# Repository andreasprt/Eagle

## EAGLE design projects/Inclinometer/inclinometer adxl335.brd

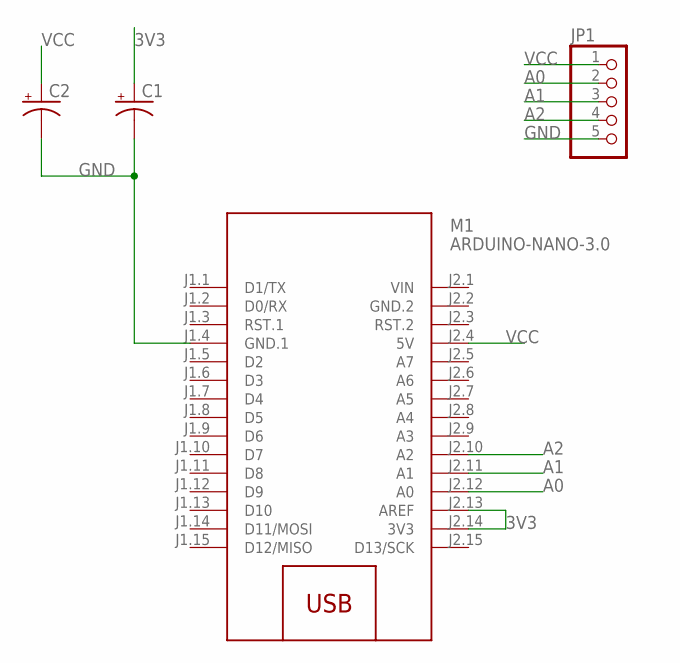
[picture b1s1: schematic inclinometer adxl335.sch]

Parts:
C1, C2: CPOL-USE2.5-6; E2,5-6
JP1: PINHD-1X5; 1X05
M1: ARDUINO-NANO-3.0

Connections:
3V3: C1.+, M1.J2.13 (AREF), M1.J2.14 (3V3)
A0: JP1.2, M1.J2.12 (A0)
A1: JP1.3, M1.J2.11 (A1)
A2: JP1.4, M1.J2.10 (A2)
GND: C1.-, C2.-, JP1.5, M1.J1.4 (GND.1)
GND.2: M1.J2.2 (GND.2)
VCC: C2.+, JP1.1, M1.J2.4 (5V)
VIN: M1.J2.1 (VIN)

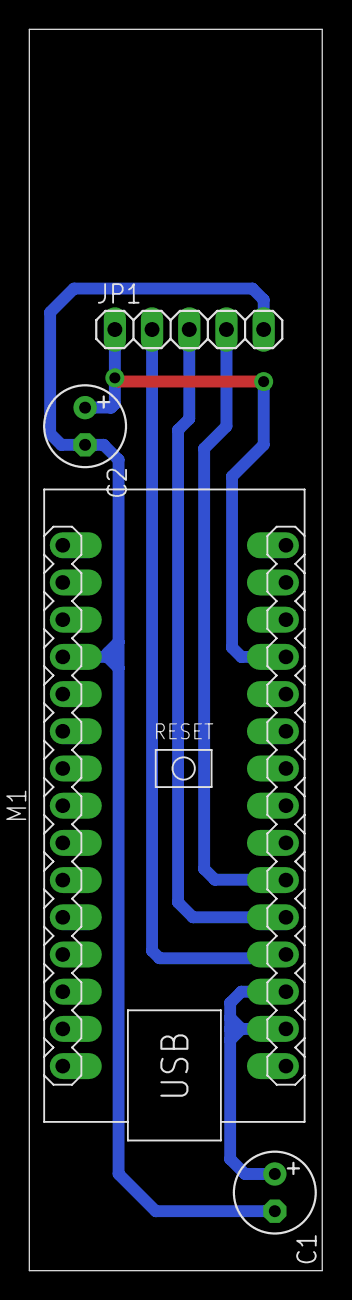
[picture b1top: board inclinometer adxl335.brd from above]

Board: 2 copper layers, 20.0 x 84.8 mm, 4 parts (0 on the bottom side), 6 nets.

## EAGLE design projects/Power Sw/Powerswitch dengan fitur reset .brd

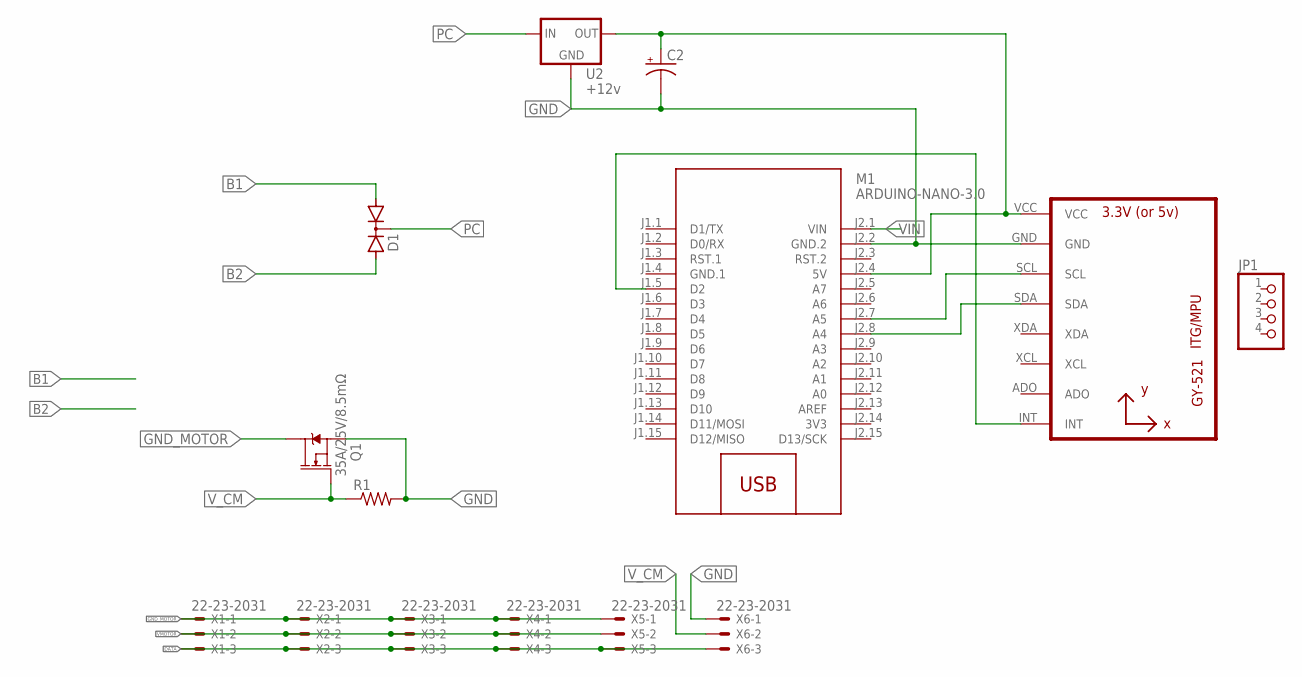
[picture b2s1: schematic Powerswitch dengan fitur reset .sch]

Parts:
C2: CPOL-USE2-5; E2-5
D1: DIODE-2AC|CATO220H; TO220AB
JP1: PINHD-1X4; 1X04
M1: ARDUINO-NANO-3.0
Q1: 35A/25V/8.5mΩ; DPAK
R1: R-US_0207/10; 0207/10
U1: GY-521MPU6050; GY-521
U2: +12v; TO-252
X1, X2, X3, X4, X5, X6: 22-23-2031

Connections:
3V3: M1.J2.14 (3V3)
B1: D1.A1
B2: D1.A2
DATA: X1.3, X2.3, X3.3, X4.3, X5.3, X6.3
GND: C2.-, M1.J2.2 (GND.2), Q1.3 (S), R1.2, U1.GND, U2.3 (GND), X6.1
GND.1: M1.J1.4 (GND.1)
GND_MOTOR: Q1.4 (D), X1.1, X2.1, X3.1, X4.1, X5.1
unnamed: M1.J2.8 (A4), U1.SDA
unnamed: M1.J2.7 (A5), U1.SCL
unnamed: M1.J1.5 (D2), U1.INT
unnamed: C2.+, M1.J2.4 (5V), U1.VCC, U2.2 (OUT)
PC: D1.C, U2.1 (IN)
VIN: M1.J2.1 (VIN)
VMOTOR: X1.2, X2.2, X3.2, X4.2, X5.2
V_CM: Q1.1 (G), R1.1, X6.2

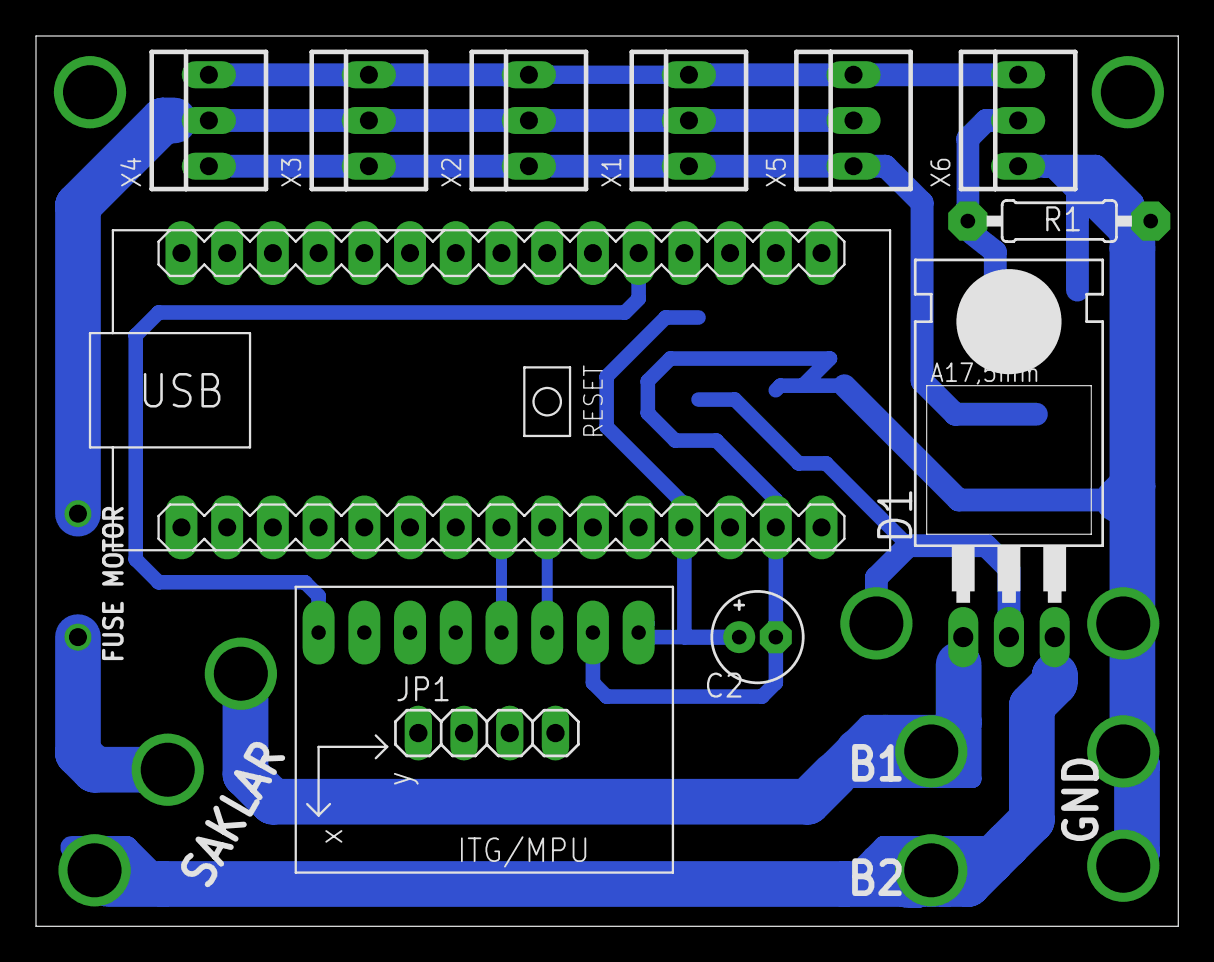
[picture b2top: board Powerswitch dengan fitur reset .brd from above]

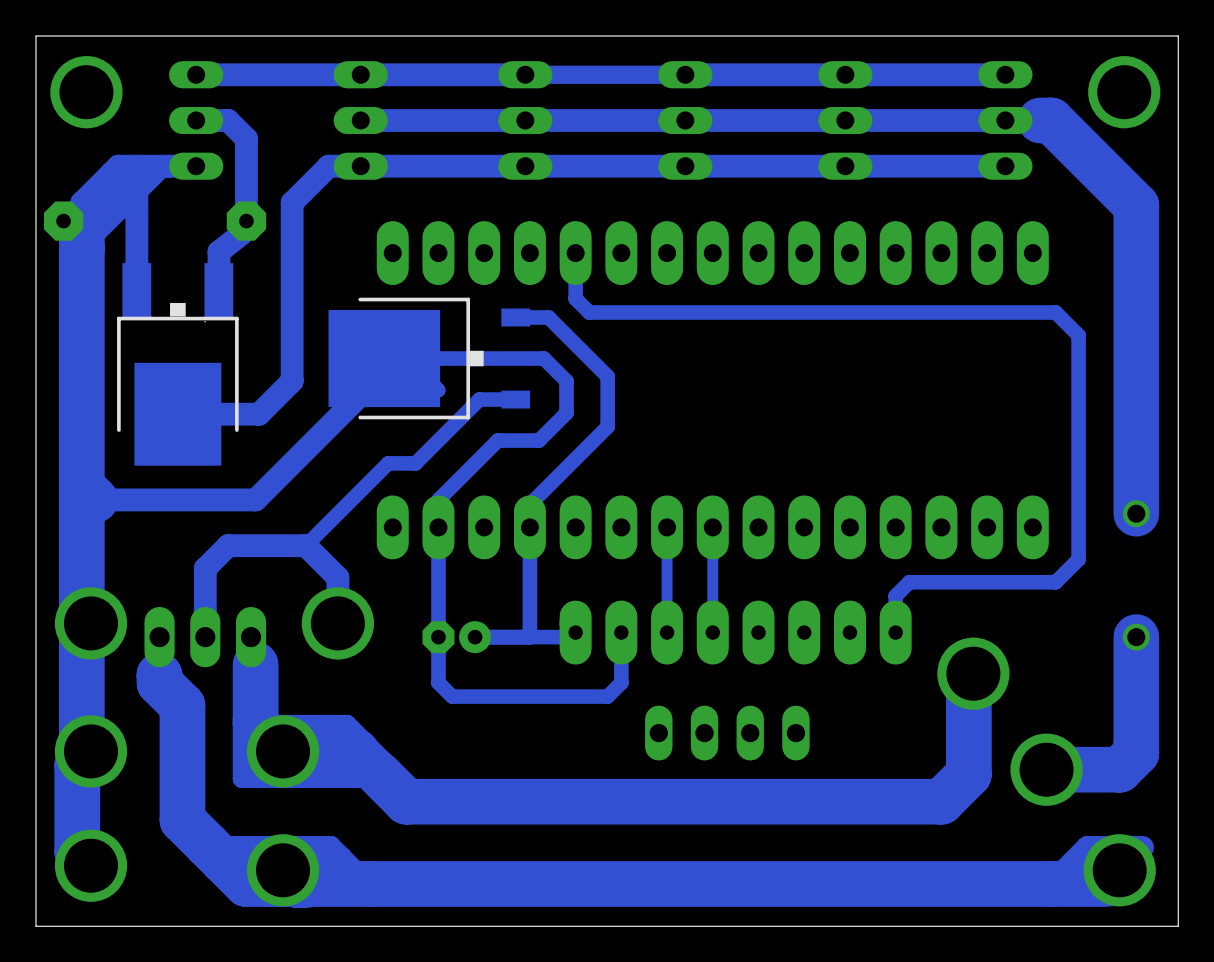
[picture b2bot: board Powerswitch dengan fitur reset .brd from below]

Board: 2 copper layers, 63.5 x 49.5 mm, 14 parts (2 on the bottom side), 10 nets.

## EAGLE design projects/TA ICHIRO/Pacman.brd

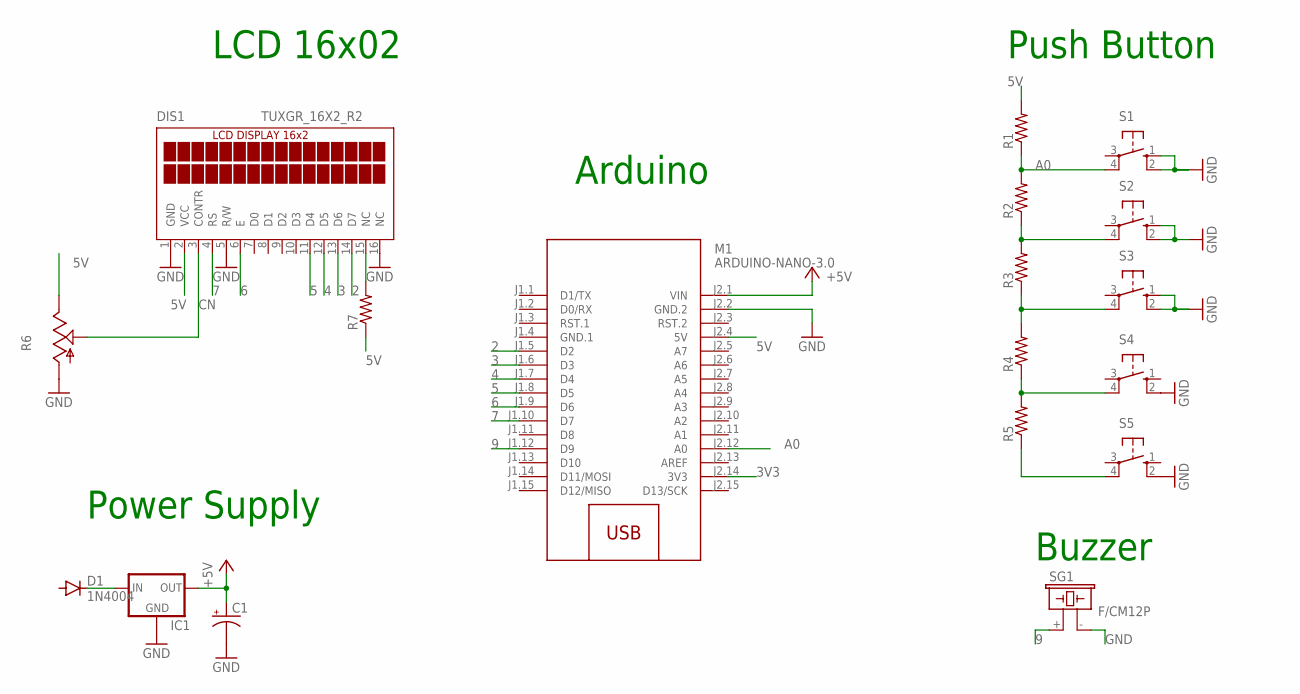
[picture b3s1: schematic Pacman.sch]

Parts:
C1: CPOL-USE2.5-6; E2,5-6
D1: 1N4004; DO41-10
DIS1: TUXGR_16X2_R2
IC1: 78XXS
M1: ARDUINO-NANO-3.0
R1, R2, R3, R4, R5, R7: R-US_0207/7; 0207/7
R6: TRIM_US-CA6V; CA6V
S1, S2, S3, S4, S5: 10-XX; B3F-10XX
SG1: F/CM12P

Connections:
2: DIS1.14 (D7), M1.J1.5 (D2)
3: DIS1.13 (D6), M1.J1.6 (D3)
3V3: M1.J2.14 (3V3)
4: DIS1.12 (D5), M1.J1.7 (D4)
5: DIS1.11 (D4), M1.J1.8 (D5)
5V: DIS1.2 (VCC), M1.J2.4 (5V), R1.2, R6.E, R7.1
6: DIS1.6 (E), M1.J1.9 (D6)
7: DIS1.4 (RS), M1.J1.10 (D7)
9: M1.J1.12 (D9), SG1.+ (1)
+5V: C1.+, IC1.OUT, M1.J2.1 (VIN)
A0: M1.J2.12 (A0), R1.1, R2.2, S1.4 (P1)
CN: DIS1.3 (CONTR), R6.S
GND: C1.-, DIS1.1 (GND), DIS1.5 (R/W), DIS1.16 (NC), IC1.GND, M1.J2.2 (GND.2), R6.A, S1.1 (S), S1.2 (S1), S2.1 (S), S2.2 (S1), S3.1 (S), S3.2 (S1), S4.2 (S1), S5.2 (S1), SG1.- (2)
GND.1: M1.J1.4 (GND.1)
unnamed: R5.1, S5.4 (P1)
unnamed: D1.C, IC1.IN
unnamed: DIS1.15 (NC), R7.2
unnamed: R2.1, R3.2, S2.4 (P1)
unnamed: R3.1, R4.2, S3.4 (P1)
unnamed: R4.1, R5.2, S4.4 (P1)

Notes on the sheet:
Arduino
LCD 16x02
Push Button
Buzzer
Power Supply

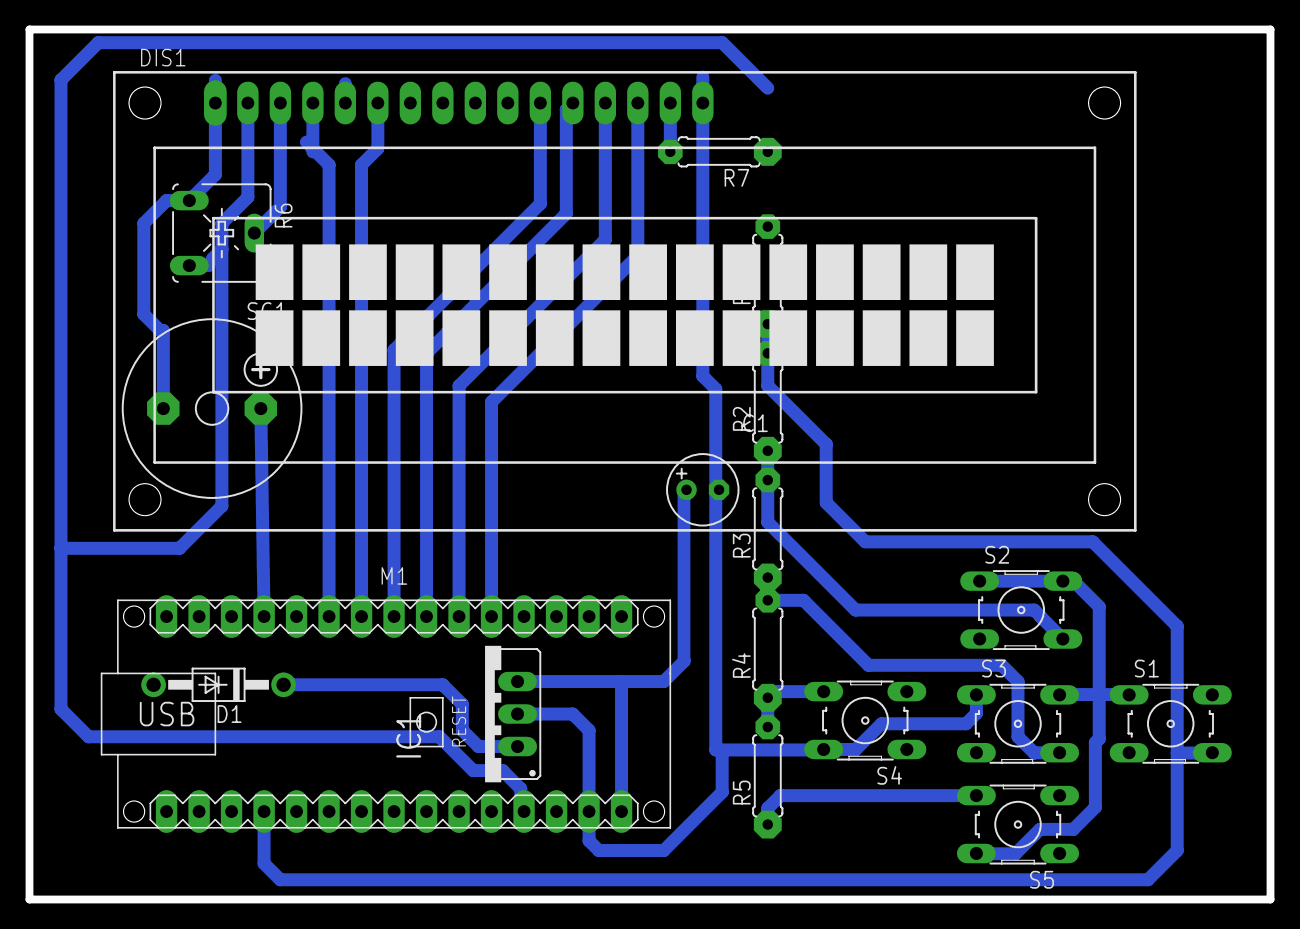
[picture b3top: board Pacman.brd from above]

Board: 2 copper layers, 97.0 x 68.0 mm, 18 parts (0 on the bottom side), 18 nets.

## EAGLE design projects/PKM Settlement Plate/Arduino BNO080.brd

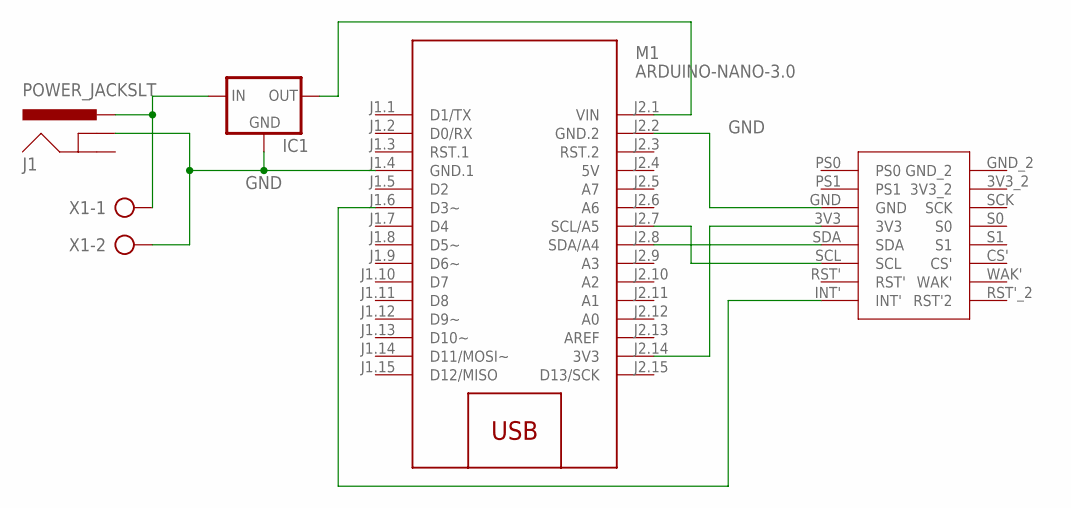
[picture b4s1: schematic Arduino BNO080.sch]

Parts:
IC1: 78XXS
J1: POWER_JACKSLT; POWER_JACK_SLOT
M1: ARDUINO-NANO-3.0
U$1: BNO080
X1: AK300/2

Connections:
5V: M1.J2.4 (5V)
GND: IC1.GND, J1.GND@1 (GNDBREAK), M1.J1.4 (GND.1), M1.J2.2 (GND.2), U$1.GND, X1.2
unnamed: M1.J2.8 (SDA/A4), U$1.SDA
unnamed: M1.J2.7 (SCL/A5), U$1.SCL
unnamed: M1.J2.14 (3V3), U$1.3V3
unnamed: M1.J1.6 (D3~), U$1.INT'
unnamed: IC1.IN, J1.PWR, X1.1
unnamed: IC1.OUT, M1.J2.1 (VIN)

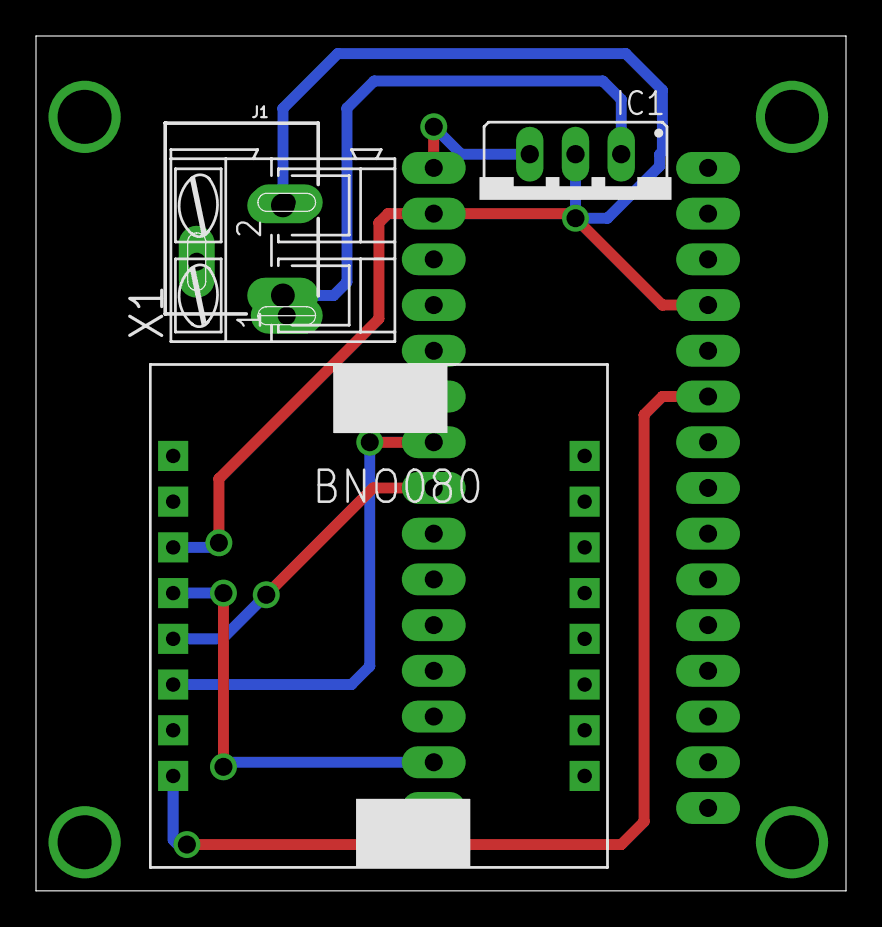
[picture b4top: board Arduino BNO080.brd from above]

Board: 2 copper layers, 45.0 x 47.5 mm, 5 parts (1 on the bottom side), 7 nets.

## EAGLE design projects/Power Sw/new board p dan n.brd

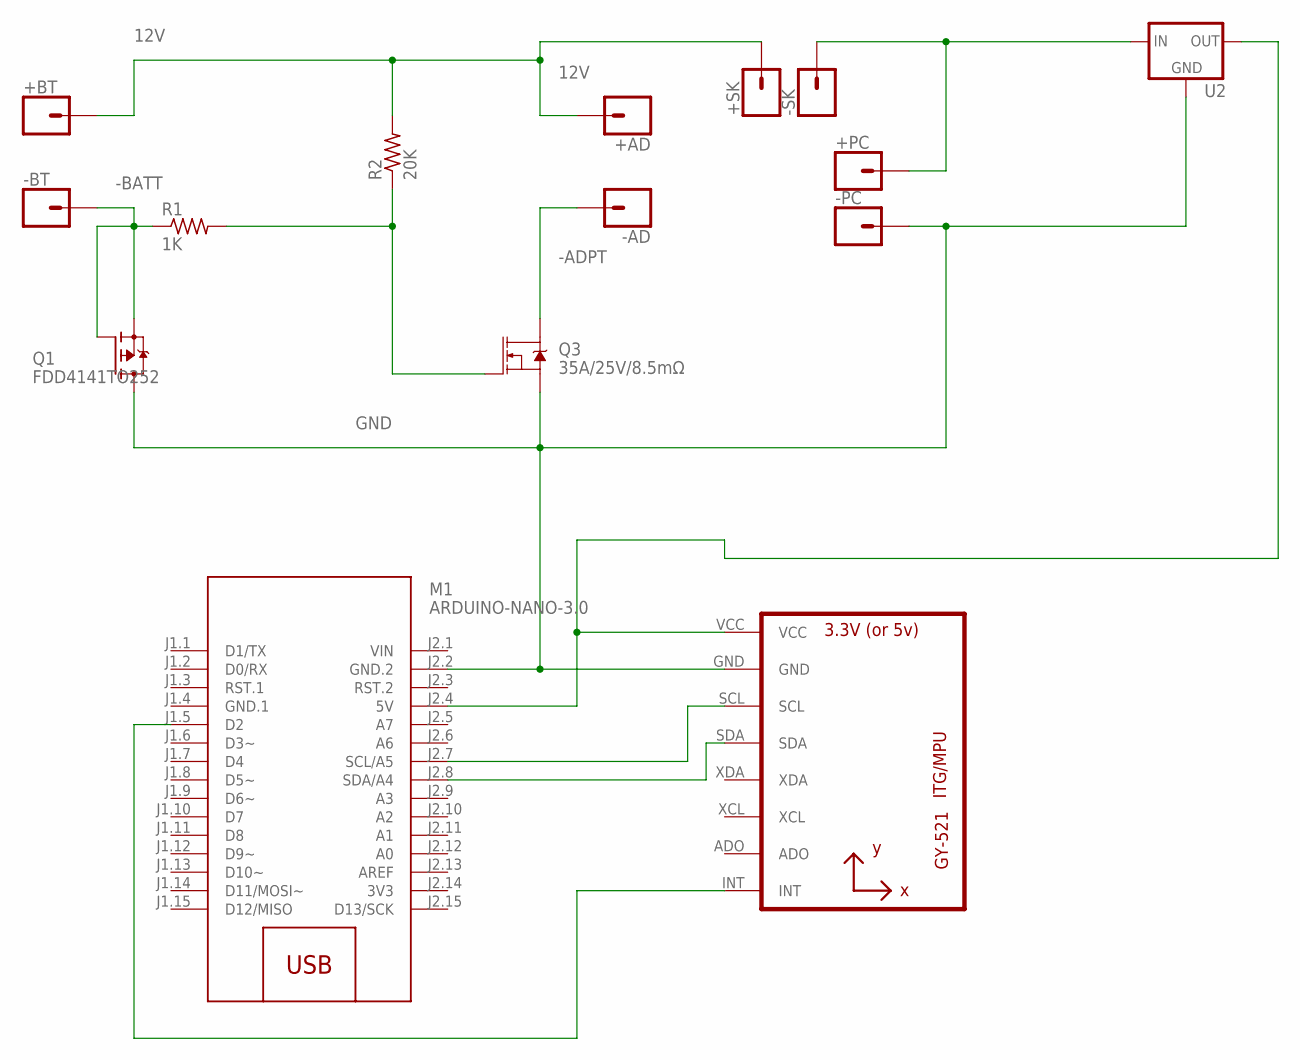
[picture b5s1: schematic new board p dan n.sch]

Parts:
+AD: CONN_01PTH_2MM; 1X01_2MM
+BT: CONN_01PTH_2MM; 1X01_2MM
+PC: CONN_01PTH_2MM; 1X01_2MM
+SK: CONN_01PTH_2MM; 1X01_2MM
-AD: CONN_01PTH_2MM; 1X01_2MM
-BT: CONN_01PTH_2MM; 1X01_2MM
-PC: CONN_01PTH_2MM; 1X01_2MM
-SK: CONN_01PTH_2MM; 1X01_2MM
M1: ARDUINO-NANO-3.0
Q1: FDD4141TO252; TO252
Q3: 35A/25V/8.5mΩ; DPAK
R1: 1K; M1206
R2: 20K; M1206
U1: GY-521MPU6050; GY-521
U2: +12v; TO-252

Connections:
3V3: M1.J2.14 (3V3)
12V: +AD.1, +BT.1, +SK.1, R2.2
-ADPT: -AD.1, Q3.4 (D)
-BATT: -BT.1, Q1.1 (G), Q1.2 (S), R1.1
GND: -PC.1, M1.J2.2 (GND.2), Q1.3 (D), Q3.3 (S), U1.GND, U2.3 (GND)
GND.1: M1.J1.4 (GND.1)
unnamed: +PC.1, -SK.1, U2.1 (IN)
unnamed: Q3.1 (G), R1.2, R2.1
unnamed: M1.J2.4 (5V), U1.VCC, U2.2 (OUT)
unnamed: M1.J2.8 (SDA/A4), U1.SDA
unnamed: M1.J2.7 (SCL/A5), U1.SCL
unnamed: M1.J1.5 (D2), U1.INT
VIN: M1.J2.1 (VIN)

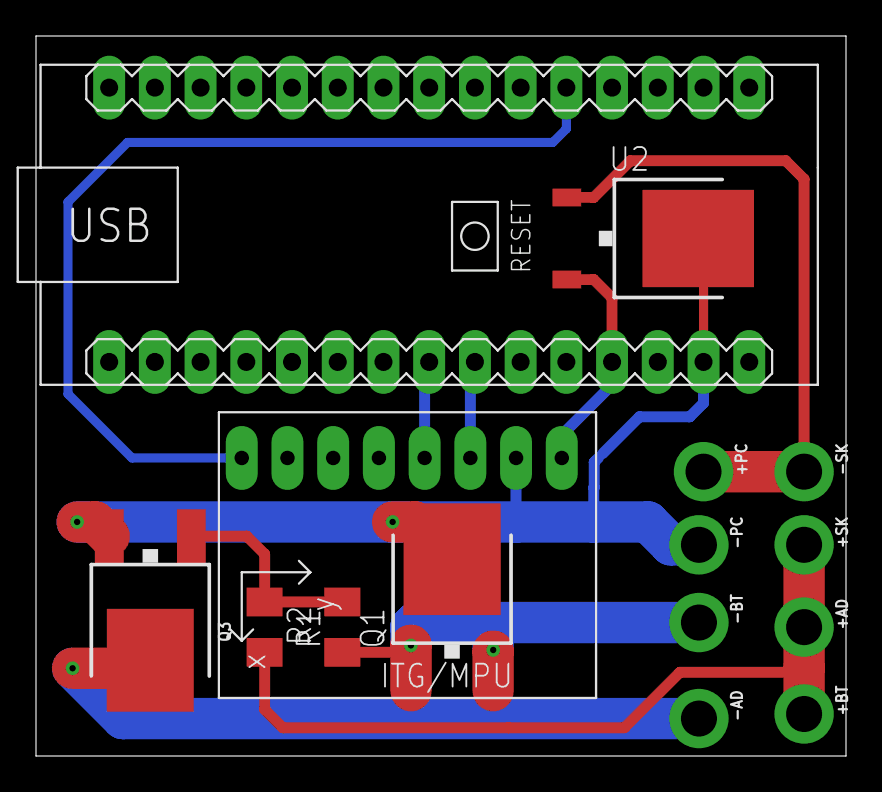
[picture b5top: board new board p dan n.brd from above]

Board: 2 copper layers, 45.0 x 40.0 mm, 15 parts (0 on the bottom side), 10 nets.

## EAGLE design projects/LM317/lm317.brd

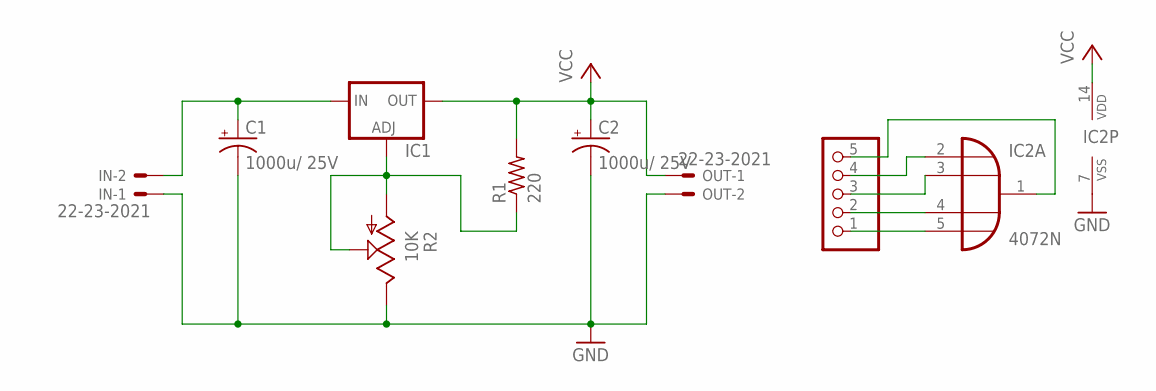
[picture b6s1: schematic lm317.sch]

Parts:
C1, C2: 1000u/ 25V; E5-8,5
IC1: LM317TS; 317TS
IC2: 4072N; DIL14
IN: 22-23-2021
JP1: PINHD-1X5; 1X05
OUT: 22-23-2021
R1: 220; 0207/10
R2: 10K; CA6V

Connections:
GND: C1.-, C2.-, IC2.7 (VSS), IN.1, OUT.2, R2.E
unnamed: C1.+, IC1.3 (IN), IN.2
unnamed: IC2.1 (O), JP1.5
unnamed: IC1.1 (ADJ), R1.1, R2.A, R2.S
unnamed: IC2.2 (I0), JP1.4
unnamed: IC2.3 (I1), JP1.3
unnamed: IC2.4 (I2), JP1.2
unnamed: IC2.5 (I3), JP1.1
VCC: C2.+, IC1.2 (OUT), IC2.14 (VDD), OUT.1, R1.2

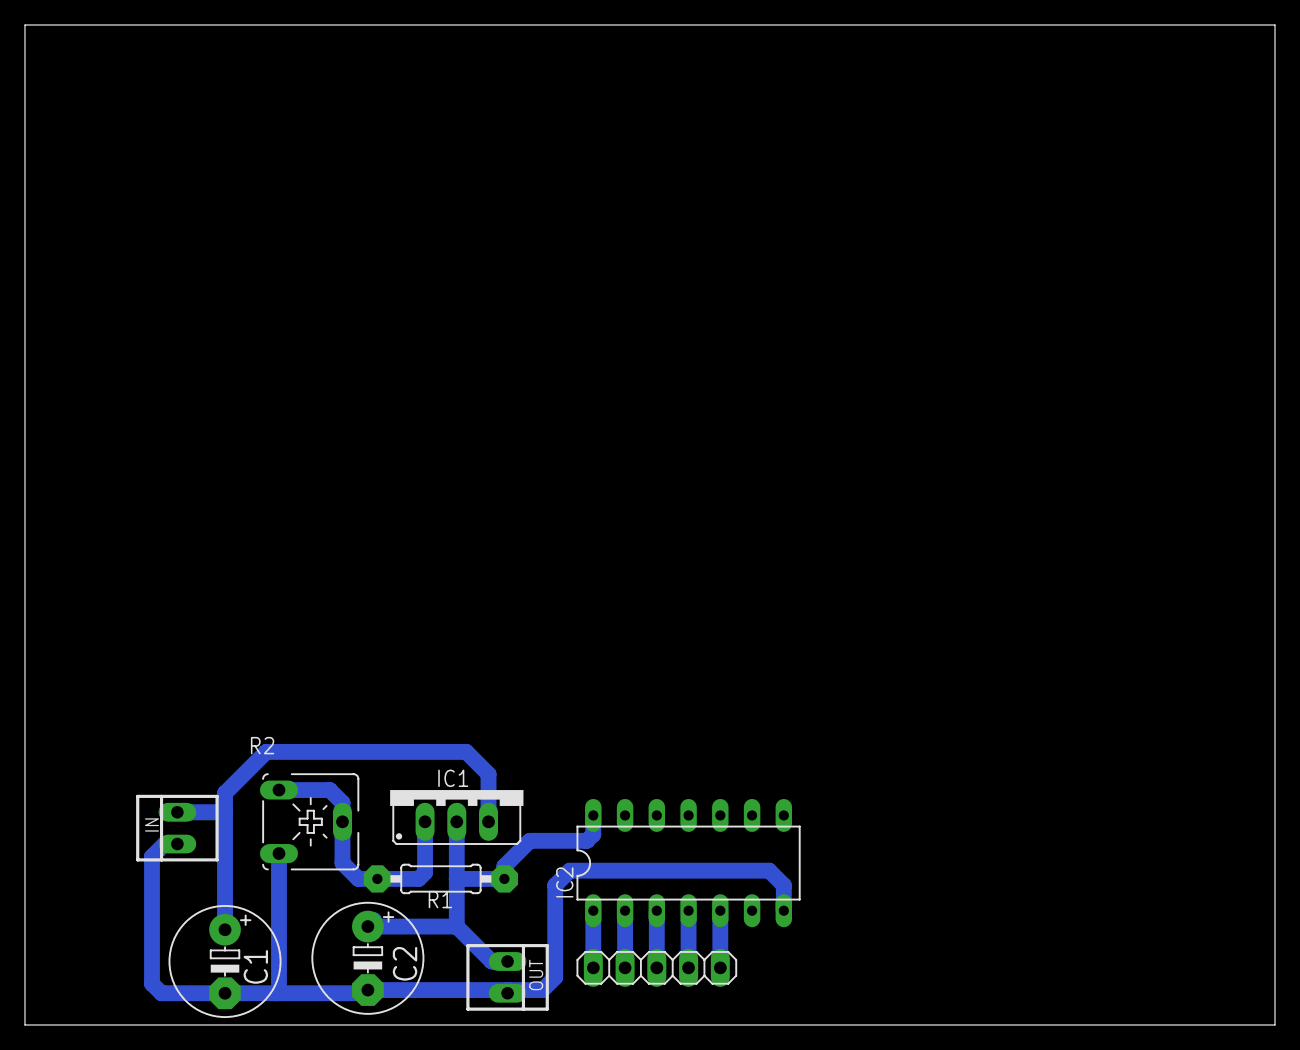
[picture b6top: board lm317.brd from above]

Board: 2 copper layers, 100.0 x 80.0 mm, 9 parts (0 on the bottom side), 9 nets.

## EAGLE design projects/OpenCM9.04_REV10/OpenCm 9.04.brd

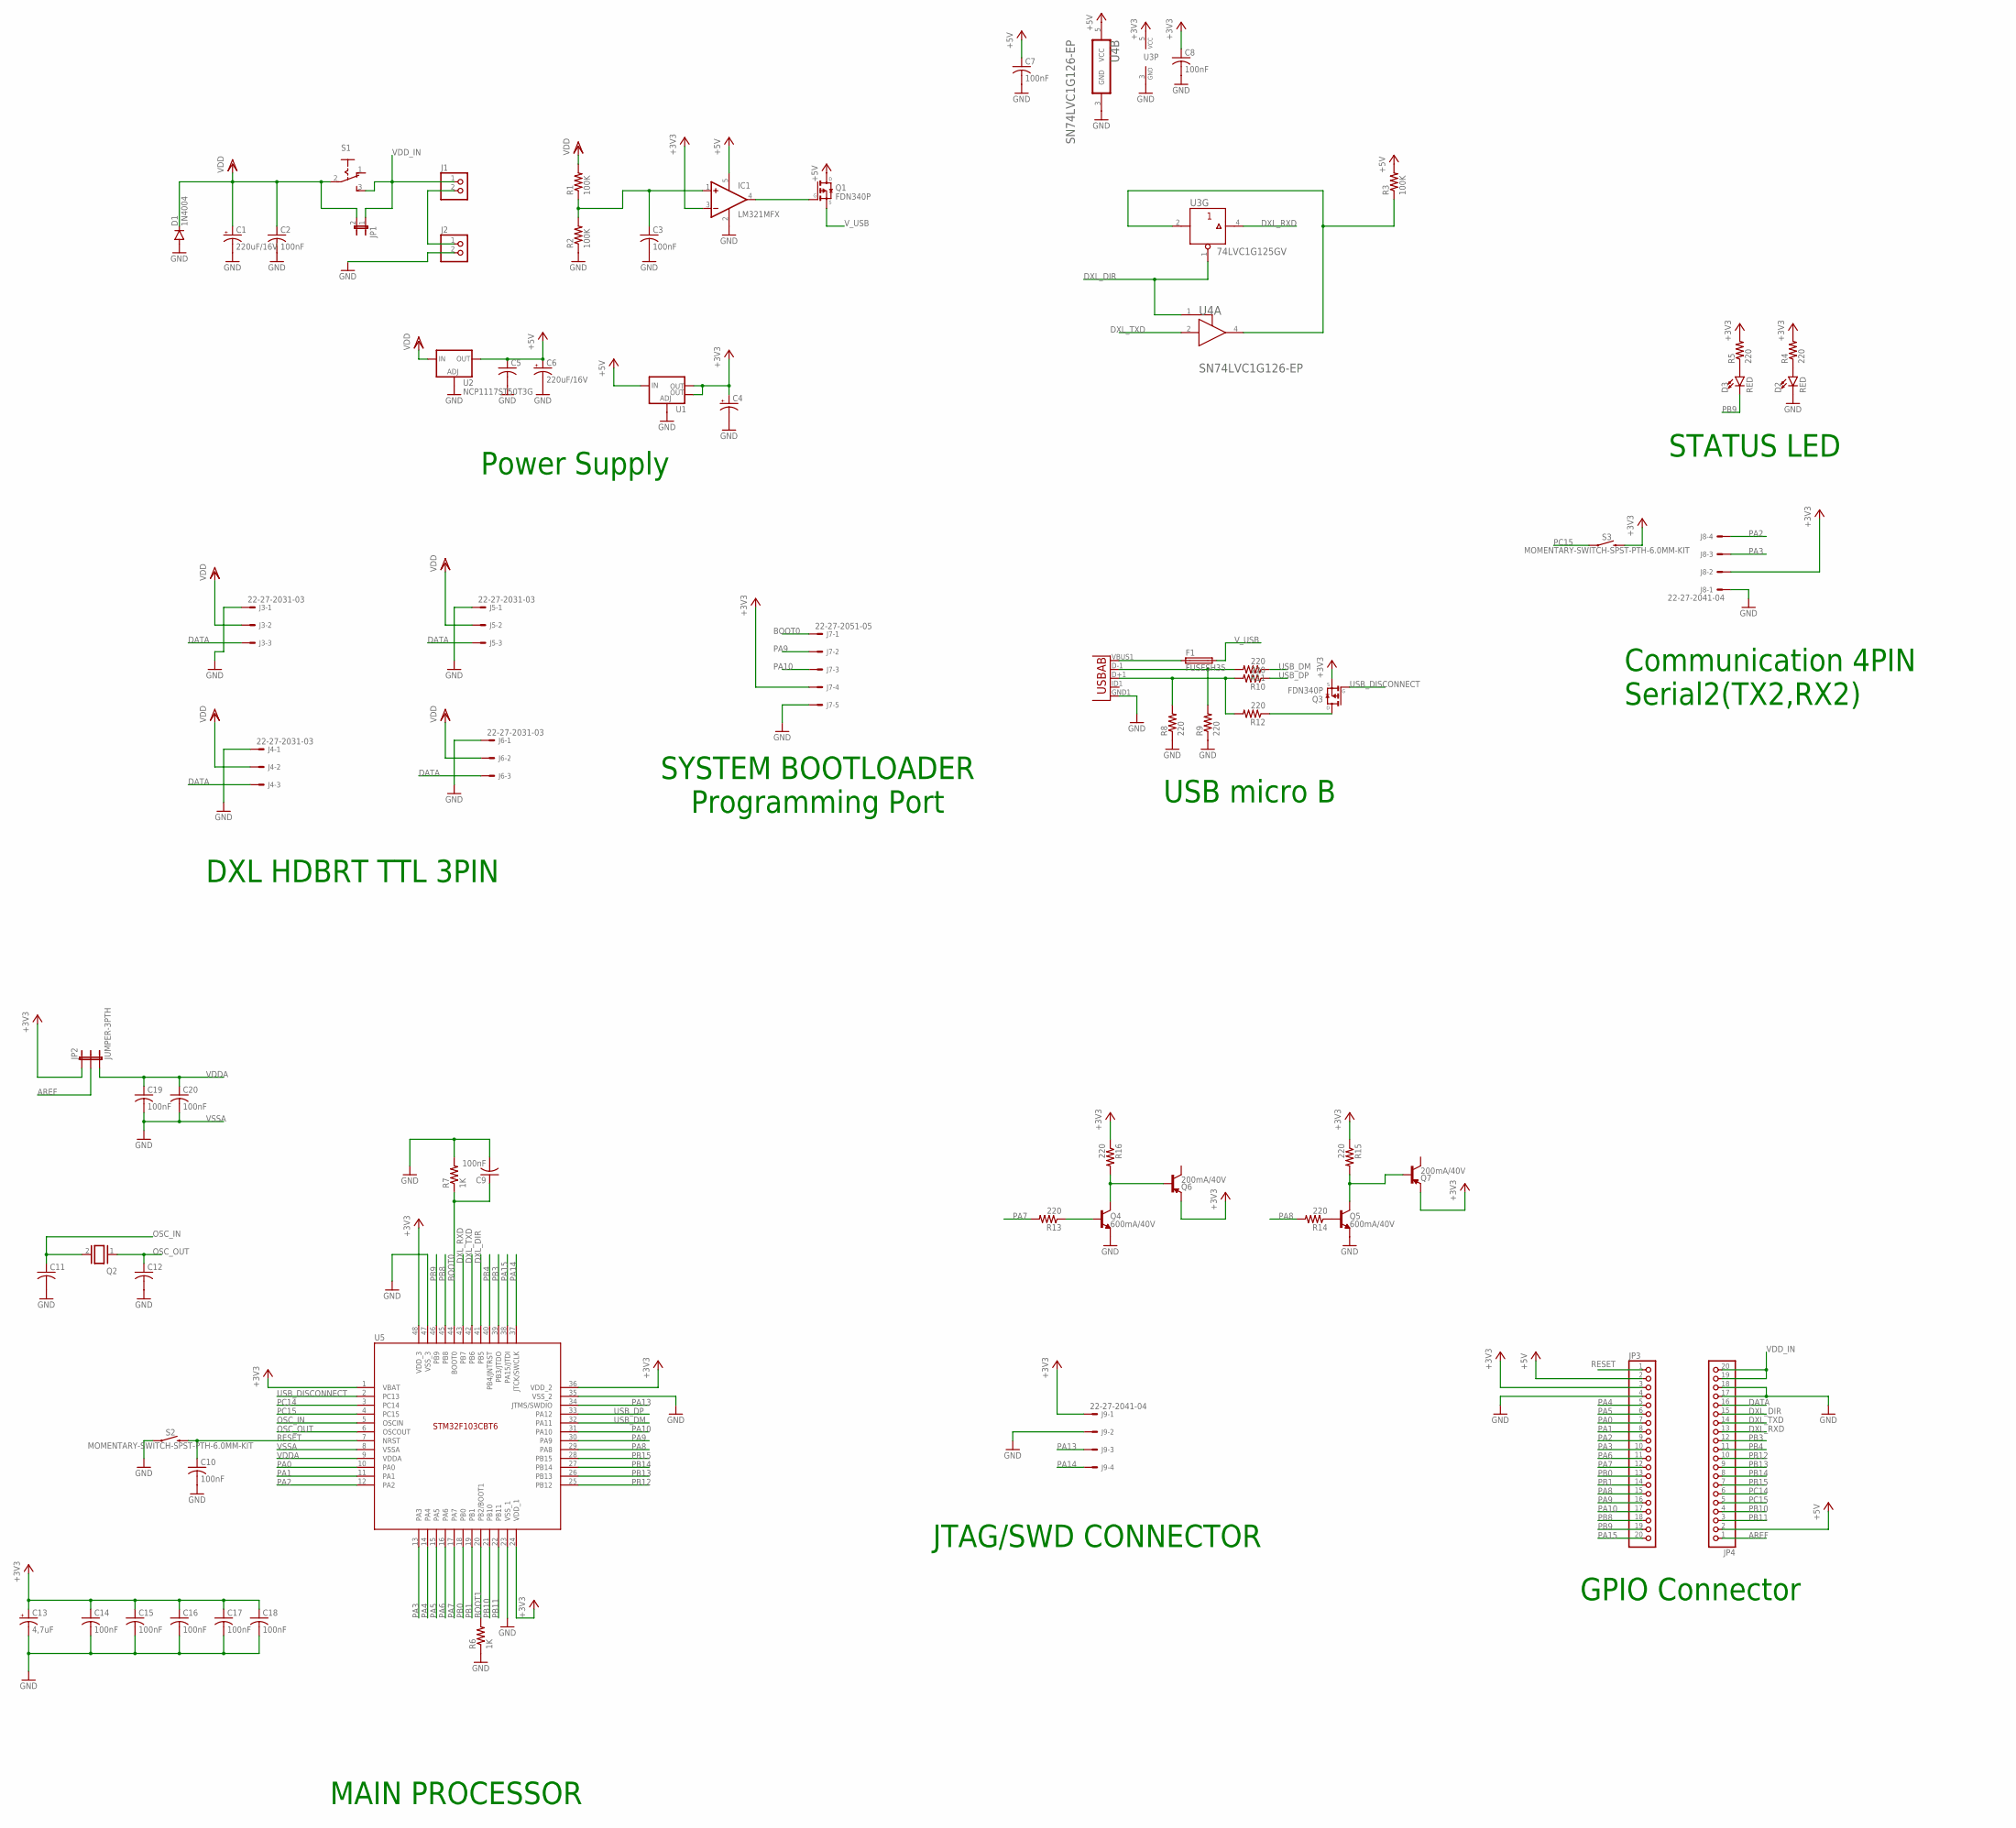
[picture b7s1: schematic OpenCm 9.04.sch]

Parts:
C1, C6: 220uF/16V; 153CLV-0810
C2, C3, C7, C8, C9, C10, C14, C15, C16, C17, C18, C19, C20: 100nF; C3216
C4: CPOL-USA/3216-18R; A/3216-18R
C5: C-USC3216; C3216
C11, C12: C-US025-025X050; C025-025X050
C13: 4,7uF; 153CLV-0810
D1: 1N4004; DO41-10
D2, D3: RED; LED-1206
F1: FUSESH35; SH25
IC1: LM321MFX; SOT23-5
J1, J2: PINHD-1X2; 1X02
J3, J4, J5, J6: 22-27-2031-03; 6410-03
J7: 22-27-2051-05; 6410-05
J8, J9: 22-27-2041-04; 6410-04
JP1: JUMPER-2PTH; 1X02
JP2: JUMPER-3PTH; 1X03
JP3, JP4: PINHD-1X20; 1X20
Q1, Q3: FDN340P; SSOT-3
Q2: XTAL/S; QS
Q4, Q5: 600mA/40V; SOT23-3
Q6, Q7: 200mA/40V; SOT23-3
R1, R2, R3: 100K; R1206
R4, R5, R8, R9, R10, R11, R12, R13, R14, R15, R16: 220; R1206
R6, R7: 1K; R1206
S1: 255SB
S2, S3: MOMENTARY-SWITCH-SPST-PTH-6.0MM-KIT; TACTILE_SWITCH_PTH_6.0MM_KIT
U1: V_REG_LM1117SOT223; SOT223
U2: NCP1117ST50T3G; SOT223
U3: 74LVC1G125GV; SOT753
U4: TEXAS_INSTRUMENTS_SN74LVC1G126-EPTEXAS_INSTRUMENT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; TEXAS_INSTRUMENTS_SN74LVC1G126-EP_1
U5: STM32F103CBT6; LQFP48
U6: USB""; USB-MICRO-SMD

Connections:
+3V3: C4.+, C8.1, C13.+, C14.1, C15.1, C16.1, C17.1, C18.1, IC1.3 (-IN), J7.4, J8.2, J9.1, JP2.1, JP3.3, Q3.2 (S), Q6.2 (E), Q7.2 (E), R4.2, R5.2, R15.1, R16.1, S3.3 (2), U1.2 (OUT), U1.4 (OUT), U3.5 (VCC), U5.1 (VBAT), U5.24 (VDD_1), U5.36 (VDD_2), U5.48 (VDD_3)
+5V: C5.1, C6.+, C7.1, IC1.5 (V+), JP3.2, JP4.2, Q1.3 (D), R3.2, U1.3 (IN), U2.2 (OUT), U4.5 (VCC)
AREF: JP2.2, JP4.1
BOOT0: C9.1, J7.1, R7.1, U5.44 (BOOT0)
BOOT1: R6.2, U5.20 (PB2/BOOT1)
DATA: J3.3, J4.3, J5.3, J6.3, JP4.16
DXL_DIR: JP4.15, U3.1 (OEN), U4.1 (OE), U5.41 (PB5)
DXL_RXD: JP4.13, U3.4 (Y), U5.43 (PB7)
DXL_TXD: JP4.14, U4.2 (A), U5.42 (PB6)
GND: C1.-, C2.2, C3.2, C4.-, C5.2, C6.-, C7.2, C8.2, C9.2, C10.2, C11.2, C12.2, C13.-, C14.2, C15.2, C16.2, C17.2, C18.2, D1.A, D2.C, IC1.2 (V-), J2.2, J3.1, J4.1, J5.1, J6.1, J7.5, J8.1, J9.2, JP3.4, JP4.17, JP4.18, Q4.2 (E), Q5.2 (E), R2.1, R6.1, R7.2, R8.1, R9.1, S2.1, U1.1 (ADJ), U2.1 (ADJ), U3.3 (GND), U4.3 (GND), U5.23 (VSS_1), U5.35 (VSS_2), U5.47 (VSS_3), U6.GND1 (GND)
unnamed: C3.1, IC1.1 (+IN), R1.1, R2.2
unnamed: R3.1, U3.2 (A), U4.4 (Y)
unnamed: J1.2, J2.1
unnamed: IC1.4 (OUT), Q1.1 (G)
unnamed: D2.A, R4.1
unnamed: D3.A, R5.1
unnamed: Q3.3 (D), R12.1
unnamed: R8.2, R10.2, R12.2, U6.D+1 (D+)
unnamed: R9.2, R11.2, U6.D-1 (D-)
unnamed: F1.1, U6.VBUS1 (VBUS)
unnamed: Q5.1 (B), R14.1
unnamed: Q5.3 (C), Q7.1 (B), R15.2
unnamed: Q4.3 (C), Q6.1 (B), R16.2
unnamed: Q4.1 (B), R13.1
OSC_IN: C11.1, Q2.2, U5.5 (OSCIN)
OSC_OUT: C12.1, Q2.1, U5.6 (OSCOUT)
PA0: JP3.7, U5.10 (PA0)
PA1: JP3.8, U5.11 (PA1)
PA2: J8.4, JP3.9, U5.12 (PA2)
PA3: J8.3, JP3.10, U5.13 (PA3)
PA4: JP3.5, U5.14 (PA4)
PA5: JP3.6, U5.15 (PA5)
PA6: JP3.11, U5.16 (PA6)
PA7: JP3.12, R13.2, U5.17 (PA7)
PA8: JP3.15, R14.2, U5.29 (PA8)
PA9: J7.2, JP3.16, U5.30 (PA9)
PA10: J7.3, JP3.17, U5.31 (PA10)
PA13: J9.3, U5.34 (JTMS/SWDIO)
PA14: J9.4, U5.37 (JTCK/SWCLK)
PA15: JP3.20, U5.38 (PA15/JTDI)
PB0: JP3.13, U5.18 (PB0)
PB1: JP3.14, U5.19 (PB1)
PB3: JP4.12, U5.39 (PB3/JTDO)
PB4: JP4.11, U5.40 (PB4/JNTRST)
PB8: JP3.18, U5.45 (PB8)
PB9: D3.C, JP3.19, U5.46 (PB9)
PB10: JP4.4, U5.21 (PB10)
PB11: JP4.3, U5.22 (PB11)
PB12: JP4.10, U5.25 (PB12)
PB13: JP4.9, U5.26 (PB13)
PB14: JP4.8, U5.27 (PB14)
PB15: JP4.7, U5.28 (PB15)
PC14: JP4.6, U5.3 (PC14)
PC15: JP4.5, S3.1, U5.4 (PC15)
RESET: C10.1, JP3.1, S2.3 (2), U5.7 (NRST)
USB_DISCONNECT: Q3.1 (G), U5.2 (PC13)
USB_DM: R11.1, U5.32 (PA11)
USB_DP: R10.1, U5.33 (PA12)
VDD: C1.+, C2.1, D1.C, J3.2, J4.2, J5.2, J6.2, JP1.2, R1.2, S1.2, U2.3 (IN)
VDDA: C19.1, C20.1, JP2.3, U5.9 (VDDA)
VDD_IN: J1.1, JP1.1, JP4.19, JP4.20, S1.3 (S)
VSSA: C19.2, C20.2, U5.8 (VSSA)
V_USB: F1.2, Q1.2 (S)

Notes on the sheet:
Power Supply
DXL HDBRT TTL 3PIN
SYSTEM BOOTLOADER Programming Port
STATUS LED
Communication 4PIN Serial2(TX2,RX2)
USB micro B
JTAG/SWD CONNECTOR
GPIO Connector
MAIN PROCESSOR

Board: 2 copper layers, 70 parts (0 on the bottom side), 63 nets, no tracks yet.

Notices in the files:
parts and their libraries:
diy-modules: Released under the Creative Commons Attribution 4.0 International License: http://creativecommons.org/licenses/by/4.0
SparkFun-LED: Licensing: Creative Commons ShareAlike 4.0 International - https://creativecommons.org/licenses/by-sa/4.0
